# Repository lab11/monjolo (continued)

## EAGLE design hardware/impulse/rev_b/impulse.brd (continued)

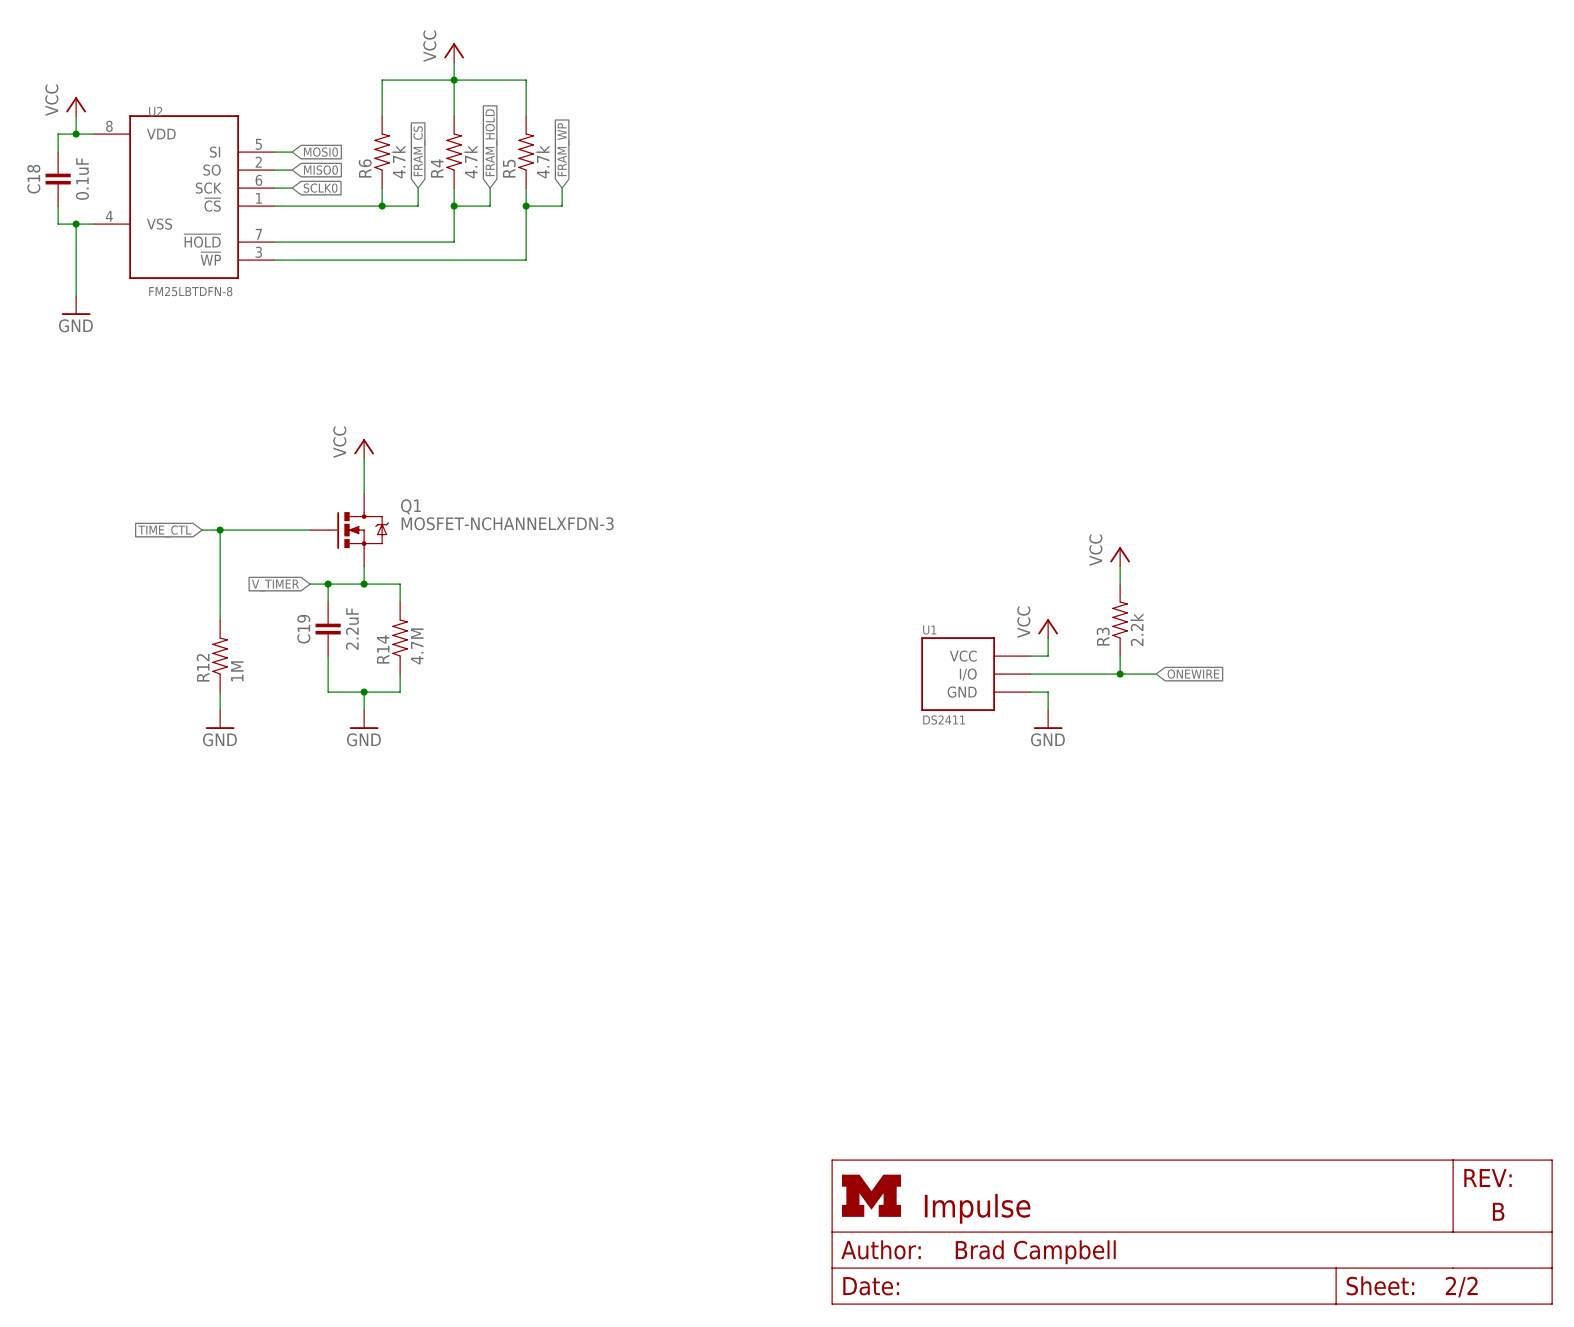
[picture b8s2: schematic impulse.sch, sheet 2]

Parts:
C18: 0.1uF; 0402_CAP
C19: 2.2uF; 0402_CAP
Q1: MOSFET-NCHANNELXFDN-3; XFDFN-3
R3: 2.2k; 0402_RES
R4, R5, R6: 4.7k; 0402_RES
R12: 1M; 0402_RES
R14: 4.7M; 0402_RES
U1: DS2411; SOT-23
U2: FM25LBTDFN-8; TDFN-8; DIGIKEY FM25L04B-DGRA-ND

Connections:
!FRAM_CS: R6.1, U2.1 (!CS); also elsewhere on the board
!FRAM_HOLD: R4.1, U2.7 (!HOLD); also elsewhere on the board
!FRAM_WP: R5.1, U2.3 (!WP); also elsewhere on the board
GND: C18.2, C19.2, R12.1, R14.1, U1.3 (GND), U2.4 (VSS); also elsewhere on the board
MISO0: U2.2 (SO); also elsewhere on the board
MOSI0: U2.5 (SI); also elsewhere on the board
ONEWIRE: R3.1, U1.1 (I/O); also elsewhere on the board
SCLK0: U2.6 (SCK); also elsewhere on the board
TIME_CTL: Q1.G, R12.2; also elsewhere on the board
VCC: C18.1, Q1.D, R3.2, R4.2, R5.2, R6.2, U1.2 (VCC), U2.8 (VDD); also elsewhere on the board
V_TIMER: C19.1, Q1.S, R14.2; also elsewhere on the board

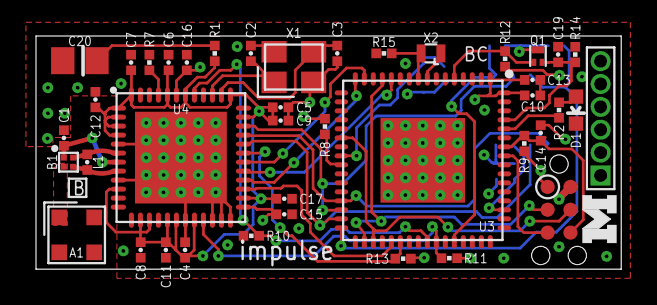
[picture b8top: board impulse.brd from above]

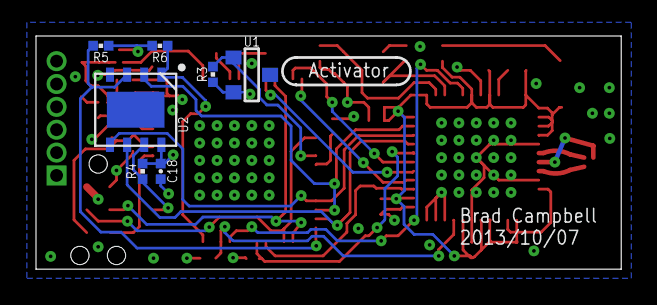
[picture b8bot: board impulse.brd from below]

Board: 4 copper layers, 32.5 x 13.0 mm, 49 parts (7 on the bottom side), 36 nets.

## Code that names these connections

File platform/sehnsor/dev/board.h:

/** \addtogroup cc2538
 * @{
 *
 * \defgroup sEHnsor
 *
 * \note   Do not include this file directly. It gets included by contiki-conf
 *         after all relevant directives have been set.
 */
#ifndef BOARD_H_
#define BOARD_H_

#include "dev/gpio.h"
#include "dev/nvic.h"
/*---------------------------------------------------------------------------*/
/** \name SmartRF LED configuration
 *
 * LEDs on the SmartRF06 (EB and BB) are connected as follows:
 * - LED1 (Red)    -> PC0
 * - LED2 (Yellow) -> PC1
 * - LED3 (Green)  -> PC2
 * - LED4 (Orange) -> PC3
 *
 * LED1 shares the same pin with the USB pullup
 * @{
 */
/*---------------------------------------------------------------------------*/
/* Some files include leds.h before us, so we need to get rid of defaults in
 * leds.h before we provide correct definitions */
#undef LEDS_GREEN
#undef LEDS_YELLOW
#undef LEDS_RED
#undef LEDS_CONF_ALL

/* Notify various examples that we do not have LEDs */
#define PLATFORM_HAS_LEDS        0
/** @} */
/*---------------------------------------------------------------------------*/
/** \name USB configuration
 *
 * The USB pullup is driven by PC0 and is shared with LED1
 */
#define USB_PULLUP_PORT          GPIO_C_BASE
#define USB_PULLUP_PIN           0
#define USB_PULLUP_PIN_MASK      (1 << USB_PULLUP_PIN)
/** @} */
/*---------------------------------------------------------------------------*/
/** \name UART configuration
 *
 * On the SmartRF06EB, the UART (XDS back channel) is connected to the
 * following ports/pins
 * - RX:  PA0
 * - TX:  PA1
 * - CTS: PB0 (Can only be used with UART1)
 * - RTS: PD3 (Can only be used with UART1)
 *
 * We configure the port to use UART0. To use UART1, change UART_CONF_BASE
 * @{
 */
#define UART_CONF_BASE           UART_0_BASE

#define UART_RX_PORT             GPIO_A_NUM
#define UART_RX_PIN              0

#define UART_TX_PORT             GPIO_A_NUM
#define UART_TX_PIN              1

#define UART_CTS_PORT            GPIO_B_NUM
#define UART_CTS_PIN             0

#define UART_RTS_PORT            GPIO_D_NUM
#define UART_RTS_PIN             3
/** @} */
/*---------------------------------------------------------------------------*/
/* Notify various examples that we do not have buttons */
#define PLATFORM_HAS_BUTTON      0
/** @} */
/*---------------------------------------------------------------------------*/
/**
 * \name Device string used on startup
 * @{
 */
#define BOARD_STRING "sEHnsor"
/** @} */

#endif /* BOARD_H_ */

/**
 * @}
 * @}
 */

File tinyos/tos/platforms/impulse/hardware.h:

/**
 * Hardware definition for the Coilcube platform.
 *
 * @author Brad Campbell
 */
#ifndef _H_hardware_h
#define _H_hardware_h

#include "msp430hardware.h"

// enum so components can override power saving,
// as per TEP 112.
enum {
  TOS_SLEEP_NONE = MSP430_POWER_ACTIVE,
};

// internal flash is 16 bits in width
typedef uint16_t in_flash_addr_t;
// external flash is 32 bits in width
typedef uint32_t ex_flash_addr_t;

void wait(uint16_t t) {
  for ( ; t > 0; t-- );
}

// LEDS
TOSH_ASSIGN_PIN(RED_LED, 6, 1);
TOSH_ASSIGN_PIN(GREEN_LED, 4, 3);
TOSH_ASSIGN_PIN(YELLOW_LED, 4, 7);

// CC2420 RADIO
TOSH_ASSIGN_PIN(RADIO_CSN, 4, 2);
TOSH_ASSIGN_PIN(RADIO_VREF, 4, 5);
TOSH_ASSIGN_PIN(RADIO_RESET, 4, 6);
TOSH_ASSIGN_PIN(RADIO_FIFOP, 1, 0);
TOSH_ASSIGN_PIN(RADIO_SFD, 4, 1);
TOSH_ASSIGN_PIN(RADIO_GIO0, 1, 3);
TOSH_ASSIGN_PIN(RADIO_FIFO, 1, 3);
TOSH_ASSIGN_PIN(RADIO_GIO1, 1, 4);
TOSH_ASSIGN_PIN(RADIO_CCA, 1, 4);

TOSH_ASSIGN_PIN(CC_FIFOP, 1, 0);
TOSH_ASSIGN_PIN(CC_FIFO, 1, 3);
TOSH_ASSIGN_PIN(CC_SFD, 4, 1);
TOSH_ASSIGN_PIN(CC_VREN, 4, 5);
TOSH_ASSIGN_PIN(CC_RSTN, 4, 6);

// USART0
TOSH_ASSIGN_PIN(SIMO0, 3, 1);
TOSH_ASSIGN_PIN(SOMI0, 3, 2);
TOSH_ASSIGN_PIN(UCLK0, 3, 3);

// USART1
TOSH_ASSIGN_PIN(SIMO1, 5, 1);
TOSH_ASSIGN_PIN(SOMI1, 5, 2);
TOSH_ASSIGN_PIN(UCLK1, 5, 3);

// UART1
TOSH_ASSIGN_PIN(UTXD0, 3, 4);
TOSH_ASSIGN_PIN(URXD0, 3, 5);
TOSH_ASSIGN_PIN(UTXD1, 3, 6);
TOSH_ASSIGN_PIN(URXD1, 3, 7);

// User Interupt Pin
TOSH_ASSIGN_PIN(USERINT, 2, 7);

// FLASH
TOSH_ASSIGN_PIN(FLASH_CS, 4, 4);

// 1-Wire
TOSH_ASSIGN_PIN(ONEWIRE, 2, 4);


void TOSH_SET_PIN_DIRECTIONS(void)
{
  P3SEL = 0x0E; // set SPI and I2C to mod func

  P1DIR = 0xe0;
  P1OUT = 0x00;

  P2DIR = 0x7b;
  P2OUT = 0x10;

  P3DIR = 0xf1;
  P3OUT = 0x00;

  P4DIR = 0xfd;
  P4OUT = 0xdd;

  P5DIR = 0xff;
  P5OUT = 0xff;

  P6DIR = 0xff;
  P6OUT = 0x00;
}

// need to undef atomic inside header files or nesC ignores the directive
#undef atomic

#endif // _H_hardware_h

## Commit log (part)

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2013-07-05 Moved coilcube source from shed
    Fixed up some naming issues and formatted for the new tinyos build
    system.
2013-07-05 Added start to rpi app for coilcube nodes
2013-07-05 Started testing persistent tcp conn
    So far it looks like it works.
2013-07-06 Added app to insert the node id in fram
    Fixed up some missing files and include folders as well.
2013-07-06 Added main coilcube app
    Need to fix the build warnings at some point.
2013-07-06 Working on coilcube packet receiver
2013-07-08 Working towards a coilcube receiver app
2013-07-08 Rewrote coilcube app
    Now has a proper state machine.
2013-07-09 Moved over and updated the load app
2013-07-09 added calibration apps
    Running the calibrate apps on the load and rpi will create a bunch of
    printf output that can be used to calibrate the coilcube.
2013-07-10 Added a version byte
    Coilcubes now transmit which version they are, in case this changes in
    the future and the wakeups mean something else. This could be useful if
    we find a way to compensate for reactive power. I'm not sure but it
    seems like a smart thing to do.
2013-07-10 Adding some pictures
2013-07-10 added resized images
2013-07-10 new sizes for images
2013-07-15 working on making coilcube ipv6 based
    Everything is in flux right now as i messed a bunch of stuff up. need to
    use the cc2420 driver for now, and then test cc2420fb once things are
    working.
2013-07-16 Updated cc2420fb to handle blip
2013-07-16 cc app with IPv6 is working
2013-07-16 App works correctly with blip and borderrouter now
2013-07-16 Correct length and seq no issues - cc2420fb
2013-07-18 Added gatd profile and correct IP
2013-07-19 added coilcube border router
    Basically a normal border router without dhcp and without rpl
2013-07-22 Added script for processing calibration data
2013-07-23 Added all the gecko power supply revisions
2013-08-02 Added app to calibrate the light sensors
2013-08-09 added documentation to monjolo d
2013-08-13 bom and new pdfs
2013-08-13 new pdf
2013-08-19 Partially removed flag from cc app
2013-08-19 Added test app for cc to make bogus data
2013-08-21 added cc power supply board
    Same form factor as the gecko power supply
2013-08-23 added full zip of cc power supply
2013-08-25 keep on improving my eagle documentation scripts
2013-08-28 better doc cc power supply a
2013-09-06 added rev e of gecko power supply
2013-09-06 Updated monjolo solar rev e
2013-09-06 new assembler with bom
2013-09-09 added coilcube rev_c
    Should be ready to be assembled
2013-09-09 umich oui!!
2013-09-09 border router config file
2013-09-09 xlsx temp files
2013-09-13 Now adds id in mac address format
2013-09-13 preparing for a coilcube purchase
2013-09-13 updated bom for gecko ps
2013-09-15 Better bom, new eagle.py script
2013-10-03 added scripts for getting cc data
2013-10-04 Split the monjolo data stuff into two files
2013-10-04 Added tinyos support for impulse
    Had to fix the clocks up and configure the led pin.
2013-10-04 added app for testing fram with blip packets
2013-10-04 added generic pins for adc
2013-10-04 added in self charge when it gets too low
2013-10-04 updated main app to use variable adc pins
2013-10-04 fixed backwardsness of led
2013-10-04 removed adc config code
2013-10-05 better zip
2013-10-08 added cad files for the cutouts for the cc cases
    The female socket needs a hole in the case.
2013-10-08 formatting boms
2013-10-08 added bom for the parts not on cc board
2013-10-09 better pdf
2013-10-09 removed TRadioAlarm
2013-10-09 put the radio driver back
2013-10-09 moved timing enums to platform specific
2013-10-09 updated platform specific to work with cc2420fb
2013-10-09 sped up clocks
2013-10-09 improved reset()
2013-10-09 updated to work with mods to cc2420fb
2013-10-09 added led blink at end of power meter application
2013-10-09 minor updates
2013-10-14 Improved monjolo app that doesn't use ipv6
2013-10-14 abstracted more of the app to be platform specific
2013-10-14 added impulse2 platform
    For the rev_b board
2013-10-14 better description of MONJOLO_VERSION
2013-10-14 more comments
2013-10-15 updated boms in excel
2013-10-15 added rev a of cc
2013-10-15 and the pdf
2013-10-15 updated pdf
2013-10-17 labels
2013-10-17 tweaks to improve label
2013-10-17 better gr
2013-10-17 more data in qr
2013-10-18 updated with changed monjolo app name
2013-10-18 spacing
2013-10-21 updated doc for impulse rev c
2013-10-23 added split core labels
2013-10-28 moved impulse to activator repo
2013-10-28 moved contiki from gecko to activator
2013-10-28 impulse rev c ready to ship
2013-10-28 updated bom with digireel
    impulse rev c
2013-11-26 use the common border router app
2013-11-26 removed the old cc receive app
2013-11-26 moved to hardware folder
2013-11-26 not sure how I got two
2013-11-26 moved to media folder
2013-11-26 moved to assembly folder
2013-11-26 moved to software folder
2013-11-26 moved gecko power supply to its folder
2013-11-26 moved into hardware folder
2013-11-26 moved to hardware
2013-11-26 moved to hardware for sehnsor
2013-11-26 moved to contiki
2013-11-26 better readme
2013-11-26 readme for hardware
2013-11-26 added description to website
2013-11-26 removed old content
2013-11-26 readme
2013-12-11 reset column
2013-12-13 update impulse info
2013-12-14 made blip default target for monjolo
    added to makefile
2013-12-14 added impulse rev c platform
2013-12-14 Updated fm25lb driver
    Rewrote it to be a state machine
    Added blocking read and write
    Updated MonjoloP to the new interface
2013-12-14 changed how id is done on impulse rev c
    id is now stored in fram (after the first reading) so there is no timing
    dependency for reading the ds2411 on each activation
2013-12-15 Fix prefix for general border router
    Need to use our customized static ip address to get the prefix
    info from the brconfig.ini file.
2013-12-15 make blip default extra
2013-12-15 updated monjolo data to use socketio
2013-12-16 updated list cc packets to socketio
2013-12-26 added screws to coilcube bom
2013-12-31 changes to hardware docs
2013-12-31 new cc docs
2014-01-09 updating coilcube zip files
2014-01-09 removed old zips
2014-01-09 new coilcube pic
2014-01-09 added mil to gitignore
2014-01-09 new impulse doc
2014-01-09 new info file
2014-01-09 more doc for rev a
2014-01-09 more doc for cc power supply a
2014-01-09 sehnsor updated
2014-01-09 impulse rev b doc
2014-01-09 impulse rev a doc
2014-01-09 gecko ps rev e doc
2014-01-09 gecko ps rev d doc
2014-01-09 gecko power supply rev c doc
2014-01-09 gecko power supply rev a doc
2014-01-13 updated doc for cc rev c
2014-01-13 no pyc
2014-01-13 updated cc bom
2014-02-04 split core label
2014-02-21 changed impulsec target to impulse-splitcore
2014-03-07 epic2 messing around
2014-03-07 new headers
2014-03-08 dummy routing for epic2
2014-03-09 rectangular board close to routed
2014-03-09 getting closer with epic2
2014-03-10 no airwaires
2014-03-10 epic2: cleaned up a couple things
2014-03-10 added comment to monjolo.h
2014-03-10 print monjolo version in the calibrate app
2014-03-10 conditionally set the monjolo version
    might also be set in the target file
2014-03-10 added epic2 header libraru
2014-03-20 updated border router app
    matches new changes to rpi tinyos
2014-03-20 updates to epic2 brd
2014-03-20 border router readme
2014-03-24 moved castellated headers in
2014-03-24 epic2/myth routed
2014-03-24 big ben
2014-03-24 updated epic2 brd
2014-03-25 bigben documentation
2014-03-25 added milling layer for panel to bigben
2014-03-26 renamed epic2 to myth
2014-04-02 receive works on cc2420fb
2014-04-09 change ds2411 address to 0
    store at beginning of fram
2014-04-09 updated monjolo app for ds2411 at the beginning
2014-04-09 added airflow sensing app
2014-04-09 adding files for breeze board
2014-04-09 some parts on breeze
2014-04-09 simple breeze board routed
    needs another pass when i get parts
2014-04-14 connectted the analog pin to the testpoint
2014-04-18 updated breeze with low pass filter
2014-04-18 added current test app for currentcoil
2014-04-24 correctly drive input from coil
2014-04-25 generate sin
2014-04-25 rough outline of what power calc looks like
2014-04-28 shipped myth
2014-04-28 shipped breeze
2014-04-28 renamed myth to atum
2014-04-28 removed myth.info
2014-04-28 remvoed myth zips
2014-04-28 shipped atum
2014-04-28 current test is looking pretty good
    based on the mechanics. no idea if it does the right thing, but the
    correct lines are getting toggled at the correct times
2014-04-30 closer, issue with sfd timing
2014-05-05 getting measurements!
2014-05-07 cleaned up current test app
2014-05-07 now send power packets on next wakeup
2014-05-08 energy harvesting coilcube++ works!!!
2014-05-08 added bom
2014-05-08 new publish files for atum
2014-05-08 added pdfs of boards
2014-05-09 added an led
2014-05-19 updated bom for bigben
2014-05-19 updated assembly images
2014-05-19 added label for gecko stack
2014-05-19 updated labels and gitignore
2014-05-19 updated coilcube fram driver
2014-05-19 removed impulse2
    old, not sure exactly what it was
2014-05-19 consolidated impulse platform
    no longer support the old version
2014-05-19 added make files for bigben
2014-05-19 updated ds2411 to new fram interface
2014-05-19 current test end with relay ctrl
2014-05-19 bigben files updated with picture
2014-05-19 working on rtc driver
2014-05-20 fixed a bunch of bugs keeping it from compiling
    fram, rtc, bigben
2014-05-20 added `make time`
    make time now adds the -RTC_ #defines to the build so we don't have
    to do the complicated thing that will does
2014-05-20 added datasheet for rtc
2014-05-20 added moteplatformc for bigben
    dont start radio all super early like
2014-05-20 fix error in decimal_to_bcd function
2014-05-20 bigben app written through state change detection
    needs serial data dump still
2014-05-20 test for time diff calculation
2014-05-20 add printout to time.extra
2014-05-20 fixed bcd_to_binary macro
2014-05-20 added test to timediff.c
2014-05-20 set storage fram output high
2014-05-20 first start at uart dump to bigben
2014-05-20 new driver for larger fram
2014-05-20 app basically feature complete
2014-05-20 other files for bigben app
2014-05-20 big ben app seems to work
2014-05-21 moved currentsampletest to gemini
2014-05-21 updated monjolo app to compile
    also fixed #ifndef in header file (finally!)
2014-05-21 add offset for programming delay
2014-05-25 documentation for atum
2014-05-25 renamed atum eagle library
2014-05-30 tunp needs to do profile id as well
2014-05-31 also rewrite profile id for berkeley
2014-05-31 moved atum to atum repository
2014-06-24 updated script for retreiving bigben data
    better handling of "hello" message at beginning and a helpful comment
    block
2014-06-25 add scripts and data from test
2014-07-12 add buzz target
2014-07-30 breeze target
2014-07-30 added hotspring board
2014-08-01 better error checking when downloading bigben
2014-08-01 renamed breeze
2014-08-01 updated to generic tasklet
2014-08-01 updated airflow app
2014-08-01 added buzz app
2014-08-06 added rev b with transistor correct
2014-08-30 hot spring updates
2014-08-30 added hotspring monjolo id
2014-09-05 added readme
2014-09-05 added blast board based on nrf51822
    in the activator series
2014-09-08 not sure what i changed
2014-09-20 blast
2014-09-24 addes squall
2014-09-25 squall mostly routed
2014-09-26 squall routed
2014-09-29 added 32khz crystal to squall
2014-09-29 getting close, real close to shipping squall
2014-09-30 silkscreen
2014-10-03 moved squall to new repo
2014-10-03 blast routed
2014-12-17 Updating GATD URL to gatd.eecs
2016-07-03 update to bigger solar panel
    - add footprint for big fram
    - add footprint for rtc
2016-07-05 add blast files
2016-07-05 better build blast
2016-07-07 save changes to old monjolo ble app
2016-07-07 simple ble monjolo app working
2016-07-07 need fram driver
2016-07-07 rename monjolo simple ble app
2016-07-08 correct app folder
2016-07-08 add eddystone url and adc
2016-07-08 get rid of windows line endings
2016-07-09 update monjolo app for new blast board
2016-07-10 switch monjolo version to 8 (ligeiro)
2016-07-10 first pass on parse.js
2016-07-14 images
